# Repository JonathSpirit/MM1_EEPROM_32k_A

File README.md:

# MM1_EEPROM_32k_A

Copyright (C) 2020 Guillaume Guillet\
Licensed under CERN-OHL-W v2 or later

<table border="0px">
<tr>
<td>
This source describes Open Hardware and is licensed under the CERN-OHL-W v2 or later.
</td>
</tr>
<tr>
<td>
You may redistribute and modify this documentation and make products
using it under the terms of the CERN-OHL-W v2 (https:/cern.ch/cern-ohl).
This documentation is distributed WITHOUT ANY EXPRESS OR IMPLIED
WARRANTY, INCLUDING OF MERCHANTABILITY, SATISFACTORY QUALITY
AND FITNESS FOR A PARTICULAR PURPOSE. Please see the CERN-OHL-W v2
for applicable conditions.
</td>
</tr>
</table>

Made with [Kicad](https://kicad.org/)

## Description
A EEPROM card with 32kBytes of capacity and compatible with [MM1 standard](https://github.com/JonathSpirit/GComputer_standard).

## Status

Version :
> MM1_EEPROM_32k_A revision 1

Status :
> Not tested !

Known issues :
> (Empty)

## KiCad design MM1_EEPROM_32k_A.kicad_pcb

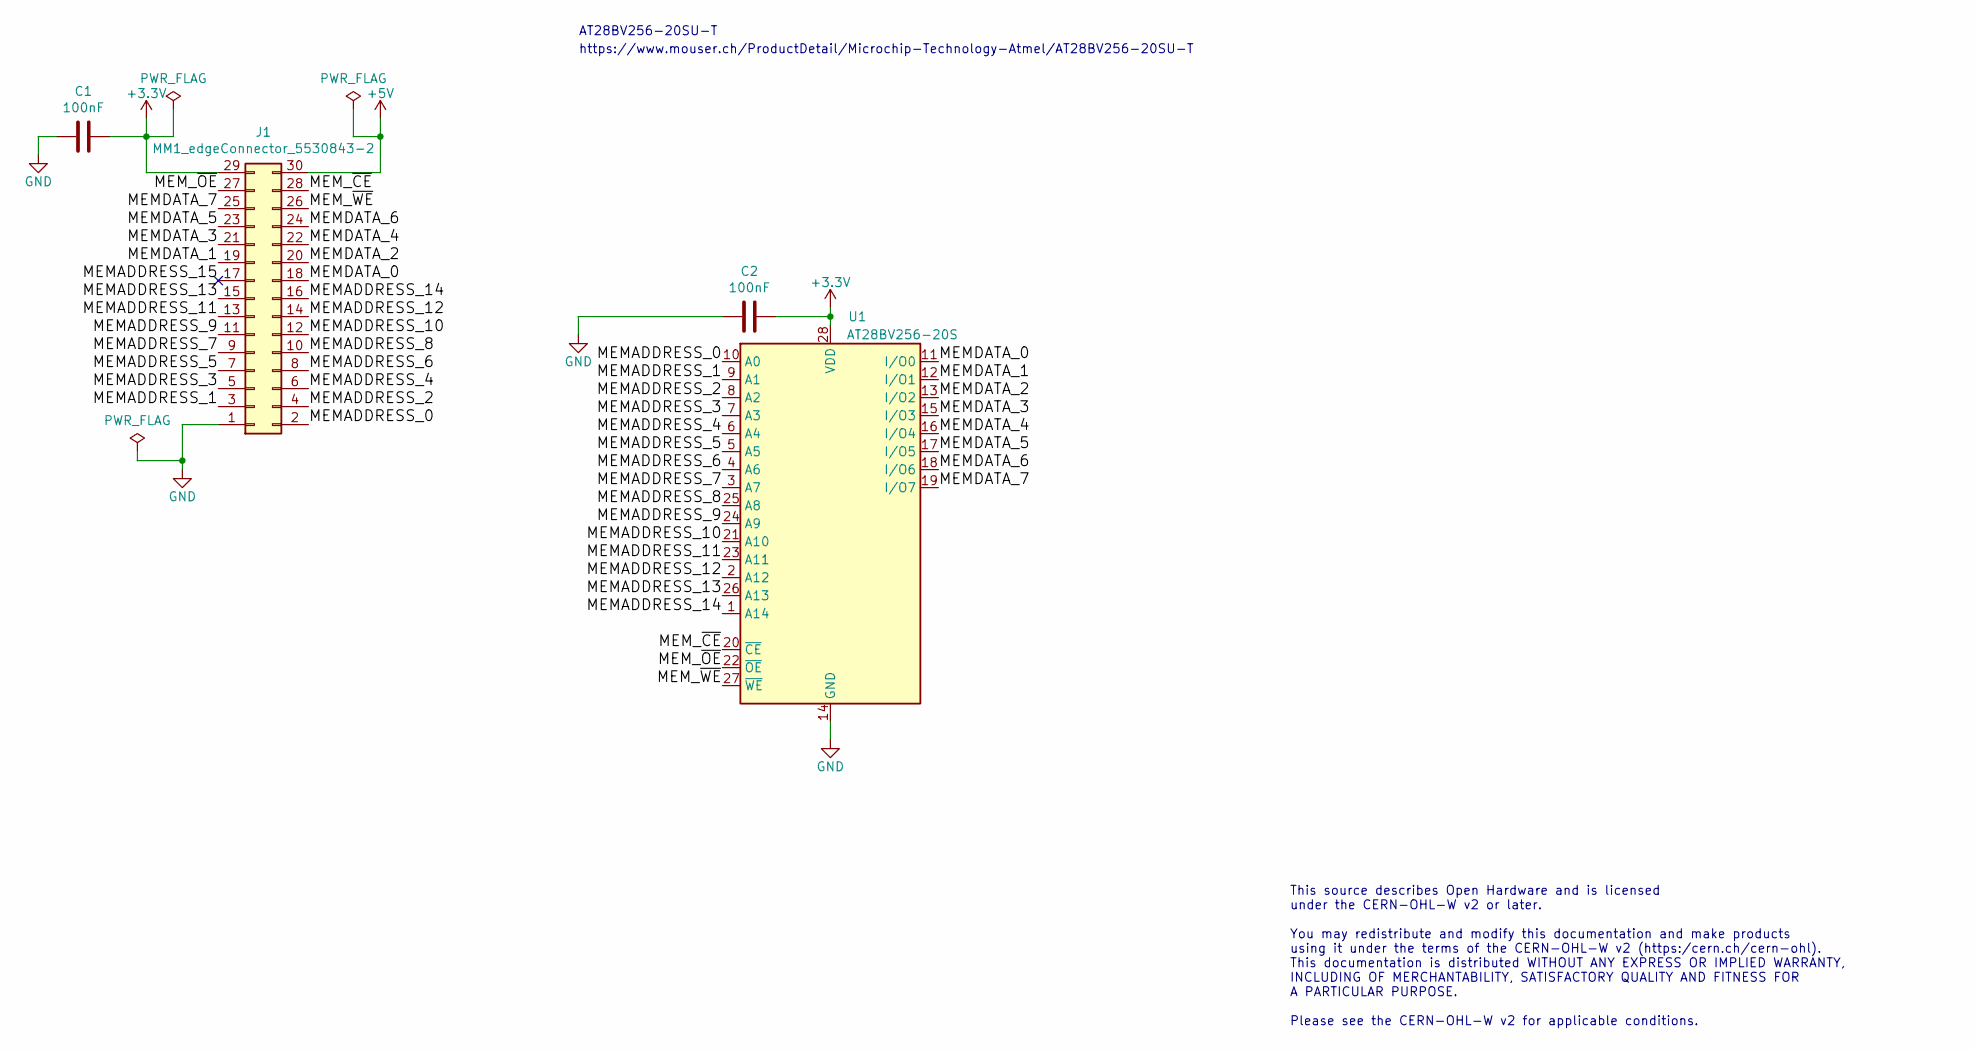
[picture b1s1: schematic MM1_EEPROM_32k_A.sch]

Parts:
C1, C2: 100nF; C_0805_2012Metric
J1: MM1_edgeConnector_5530843-2; 5530843-2_edge
U1: AT28BV256-20S; SOIC-28W_7.5x17.9mm_P1.27mm

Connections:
+3V3: C1.2, C2.1, J1.29, U1.28 (VDD)
+5V: J1.30
/MEMADDRESS_0: J1.2, U1.10 (A0)
/MEMADDRESS_1: J1.3, U1.9 (A1)
/MEMADDRESS_2: J1.4, U1.8 (A2)
/MEMADDRESS_3: J1.5, U1.7 (A3)
/MEMADDRESS_4: J1.6, U1.6 (A4)
/MEMADDRESS_5: J1.7, U1.5 (A5)
/MEMADDRESS_6: J1.8, U1.4 (A6)
/MEMADDRESS_7: J1.9, U1.3 (A7)
/MEMADDRESS_8: J1.10, U1.25 (A8)
/MEMADDRESS_9: J1.11, U1.24 (A9)
/MEMADDRESS_10: J1.12, U1.21 (A10)
/MEMADDRESS_11: J1.13, U1.23 (A11)
/MEMADDRESS_12: J1.14, U1.2 (A12)
/MEMADDRESS_13: J1.15, U1.26 (A13)
/MEMADDRESS_14: J1.16, U1.1 (A14)
/MEMADDRESS_15: J1.17
/MEMDATA_0: J1.18, U1.11 (I/O0)
/MEMDATA_1: J1.19, U1.12 (I/O1)
/MEMDATA_2: J1.20, U1.13 (I/O2)
/MEMDATA_3: J1.21, U1.15 (I/O3)
/MEMDATA_4: J1.22, U1.16 (I/O4)
/MEMDATA_5: J1.23, U1.17 (I/O5)
/MEMDATA_6: J1.24, U1.18 (I/O6)
/MEMDATA_7: J1.25, U1.19 (I/O7)
/MEM_~CE: J1.28, U1.20 (~CE)
/MEM_~OE: J1.27, U1.22 (~OE)
/MEM_~WE: J1.26, U1.27 (~WE)
GND: C1.1, C2.2, J1.1, U1.14 (GND)

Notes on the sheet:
AT28BV256-20SU-T
https://www.mouser.ch/ProductDetail/Microchip-Technology-Atmel/AT28BV256-20SU-T
This source describes Open Hardware and is licensed under the CERN-OHL-W v2 or later. You may redistribute and modify this documentation and make products using it under the terms of the CERN-OHL-W v2 (https:/cern.ch/cern-ohl). This documentation is distributed WITHOUT ANY EXPRESS OR IMPLIED WARRAN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

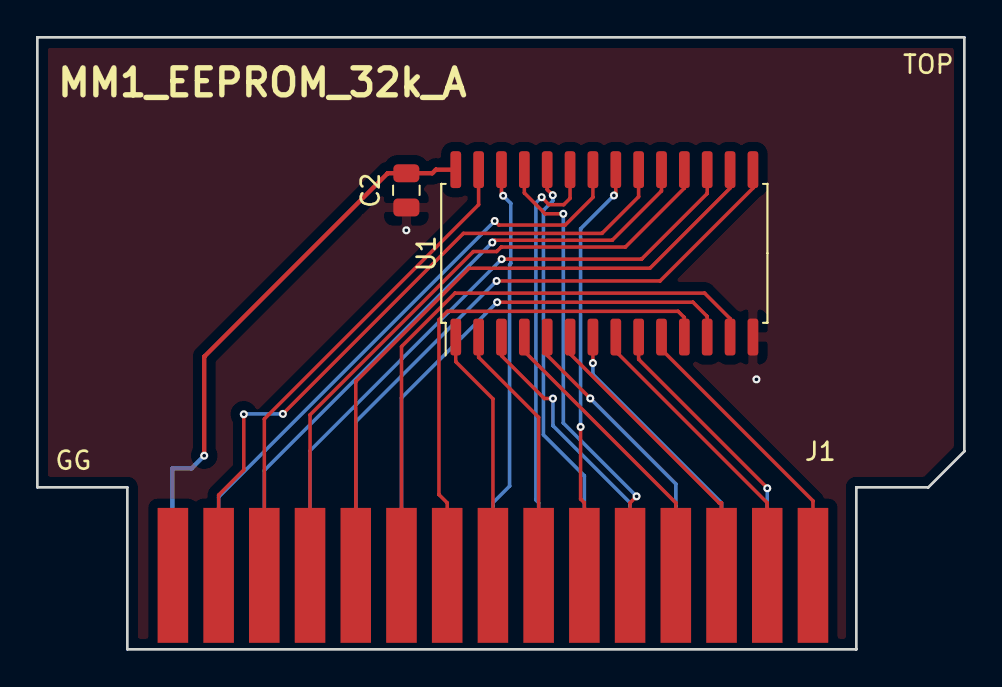
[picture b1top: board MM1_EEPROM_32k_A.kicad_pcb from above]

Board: 2 copper layers, 51.5 x 34.0 mm, 4 parts (1 on the bottom side), 28 nets.

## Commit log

2020-11-28 add .gitignore
2020-11-28 first push
2020-11-28 correct copy-paste :=)
2021-11-08 Update README.md
    https://forum.kicad.info/t/warning-avoid-all-links-to-kicad-pcb-org-use-kicad-org/31521

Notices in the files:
MM1_EEPROM_32k_A.kicad_pcb:
Copyright Guillaume Guillet 2020
